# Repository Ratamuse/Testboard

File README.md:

## Testboard V2.2 ESP32

## Carte multi-usage basée sur le module ESP-WROOM-32E:

- Connecteur USB-C

- Chargeur solaire MPPT basé sur la puce CN3791:  http://www.consonance-elec.com/pdf/datasheet/DSE-CN3791.pdf

- Connecteur batterie JST-PH 2mm avec protection (surcharge ou décharge profonde)

- Connecteur batterie JST-PH 2mm sans protection (pour batterie déjà protégée)

- Bouton on/off LTC2954 avec interrupt sur µP (On/Off de l'ESP32 et GPIO de l'interrupt utilisable pour des actions): https://www.analog.com/media/en/technical-documentation/data-sheets/2954fb.pdf

- Capteur BOSCH BME680: https://www.bosch-sensortec.com/products/environmental-sensors/gas-sensors/bme680/

- 10 optocoupleurs pour interrupteurs à contacts secs (pour domotiser volets roulants, télécommandes diverses) ou au choix 10 GPIO dispo avec au choix alim 3.3V ou "5V" (Vbat (entre 3.2 et 4.2V) ou Vbus (5V)) pour ajouter des modules.

- Chargeur Li-io/Li-Po MCP73831 via port USB-C

- Connecteur JST-PH 2mm (1x4) I2C

- Connecteur JST-PH 2mm (1x4) sur 2 GPIO + choix 3.3V ou 5V

- Connecteur JST-PH 2mm (1x3) sur 1 GPIO (que j'utilise pour piloter des leds neopixel)

Inspiration des travaux de Lilygo, Waveshare, GreatScoot.

Motivation et champs des possibles donnés par P. Demerliac et sa chaine Youtube Cyrob: https://www.youtube.com/channel/UC5QPFDZ3Y4ylkkGJc6Y1OOA  

Initiation à la bricole par P. W. Trainer

Prochaine étape, améliorer le hardaware du GNUVario-E

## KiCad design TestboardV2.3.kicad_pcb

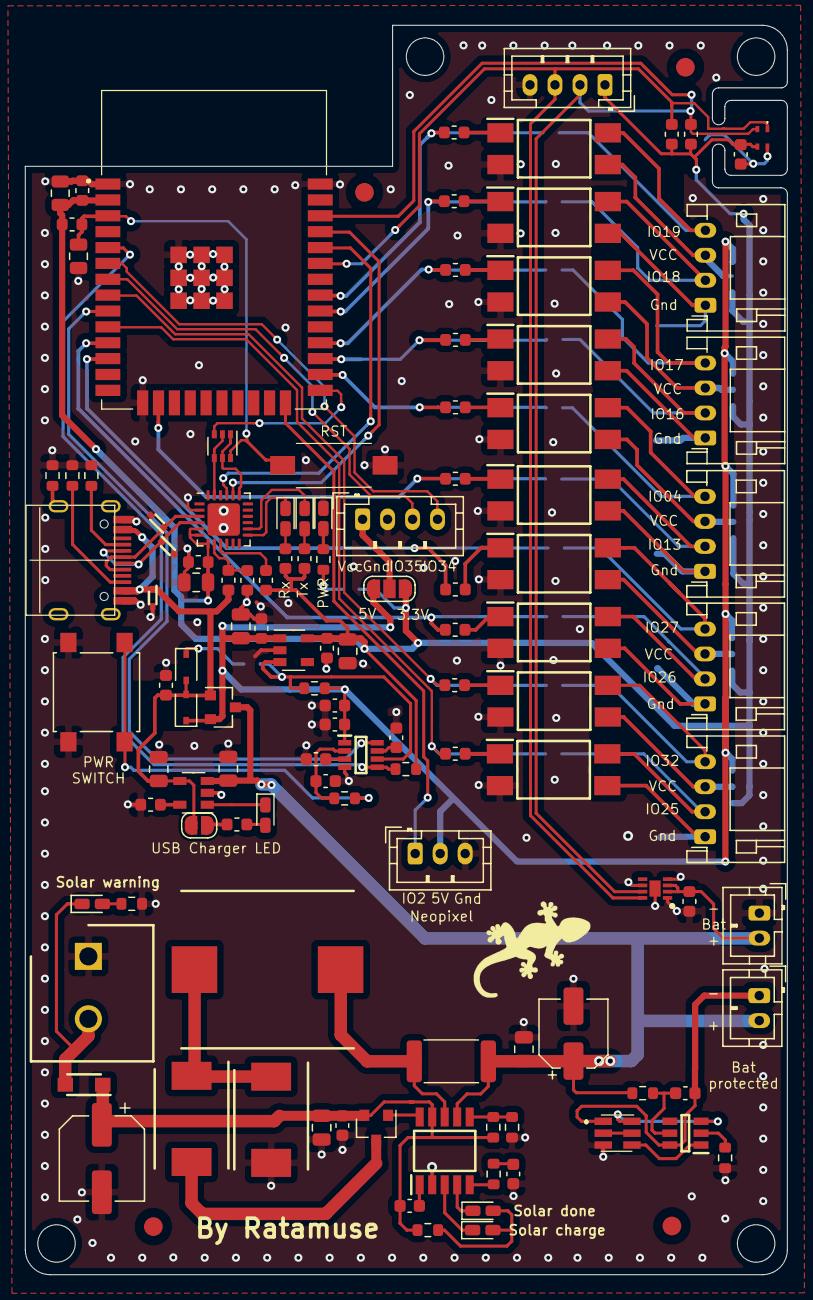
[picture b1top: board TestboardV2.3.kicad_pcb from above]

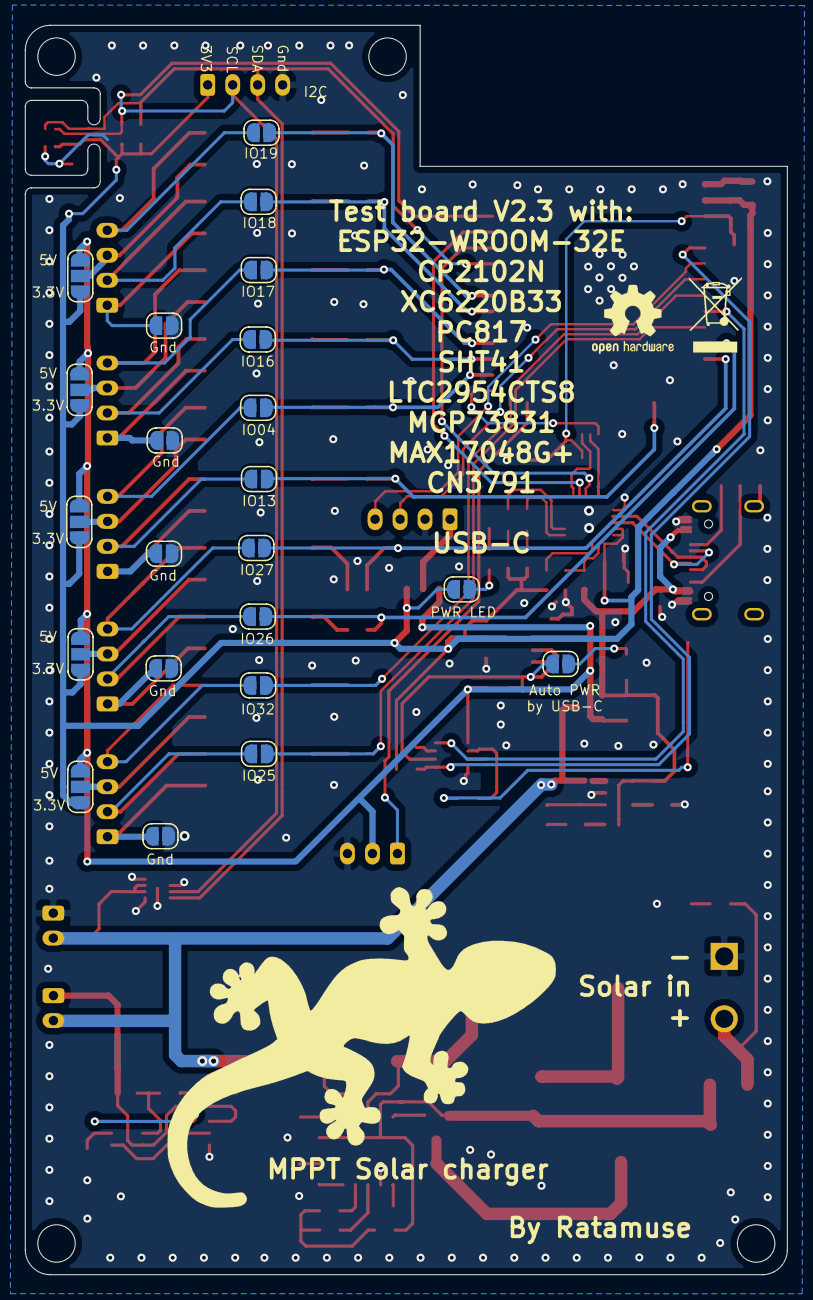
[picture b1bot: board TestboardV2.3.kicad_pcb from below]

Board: 2 copper layers, 61.0 x 100.0 mm, 143 parts (22 on the bottom side), 102 nets.

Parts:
C1, C3: 22µF; C_0805_2012Metric
C2, C5, C7, C9, C11, C15, C18, C20, C27: 0.1µF; C_0603_1608Metric
C4: 1µF; C_0603_1608Metric
C6, C16, C17: 4.7µF; C_0805_2012Metric
C8, C10: 0.150µF; C_0603_1608Metric
C12: 100µF/35V; CP_Elec_6.3x7.7
C13: 470nF/50V; C_0603_1608Metric
C14: 4.7µF/50V; C_0805_2012Metric
C19: 220nF; C_0603_1608Metric
C21: 0.1µF/50V; C_0603_1608Metric
C22, C24, C25: 10µF; C_0805_2012Metric
C23: 10µF; CP_Elec_5x5.4
D1, D2, D3: SP1003-01DTG; SODFL1406X65N
D4, D14: D_Schottky; D_SOD-323
D5, D6, D7, D8, D10, D11: LED; LED_0603_1608Metric_Castellated
D9: MBR230LSFT1G; SODFL3616X98N
D12, D13: SS34; DIOM8059X256N
D15: LED Green; LED_0603_1608Metric_Castellated
FID1, FID2, FID3, FID4: Fiducial; Fiducial_1.5mm_Mask3mm
IC1: CN3791; SOP100P600X175-10N
IC2: MAX17048G+; SON50P200X200X80-9N-D
IC3: LTC2954CTS8-1#TRMPBF; SOT65P280X100-8N
IC4: FS312F-G; SOT95P280X145-6N
IC6: SHT41-AD1B-R3; SHT41AD1BR3
J1: Conn_01x02; SHDR2W90P0X500_1X2_1060X980X1380P
J2, J3, J4, J5, J6: Conn_01x04_MountingPin; JST_PH_S4B-PH-K_1x04_P2.00mm_Horizontal_ratamuse
J7, J10: Conn_01x04; JST_PH_B4B-PH-K_1x04_P2.00mm_Vertical
J8, J12: Conn_01x02; JST_PH_B2B-PH-K_1x02_P2.00mm_Vertical
J9: Conn_01x03; JST_PH_B3B-PH-K_1x03_P2.00mm_Vertical
J13: USB_C_Receptacle_USB2.0 USB4105-GF-A; TYPE-C-31-M-12
JP1, JP2, JP3, JP4, JP5, JP6, JP7, JP8, JP9, JP10, JP11, JP12, JP15, JP16, JP17, JP21, JP24: SolderJumper_2_Open; SolderJumper-2_P1.3mm_Open_RoundedPad1.0x1.5mm
JP13, JP14, JP18, JP19, JP20, JP23: SolderJumper_3_Open; SolderJumper-3_P1.3mm_Open_RoundedPad1.0x1.5mm_NumberLabels
JP22: Jumper_2_Open; SolderJumper-2_P1.3mm_Open_RoundedPad1.0x1.5mm
L1: 82µH/3A; INDPM138126X700N
Q1: UMH3N; SOT-363_SC-70-6
Q2: DMG2301L; SOT-23
Q3: AO3401A; SOT-23
Q4: FS8205
R1, R15, R19, R25, R27, R29: 10K; R_0603_1608Metric
R2, R3, R4, R5, R6, R7, R8, R9, R10, R11, R14, R21, R22, R30: 1K; R_0603_1608Metric
R12: 22.1K; R_0603_1608Metric
R13: 47.5k; R_0603_1608Metric
R16, R17: 2.2K; R_0603_1608Metric
R18, R35: 2K; R_0603_1608Metric
R20: 330; R_0603_1608Metric
R23: 30K; R_0603_1608Metric
R24: 120; R_0603_1608Metric
R26: 1M; R_0603_1608Metric
R28: 0.24R; R_2512_6332Metric
R31: 100; R_0603_1608Metric
R33, R34, R36: 5.1K; R_0603_1608Metric
R37: 100K; R_0603_1608Metric
SW1: SW_Push; PTS636SL43SMTRLFS
SW2: SW_Push; SW_SPST_B3S-1000
U1: ESP32-WROOM-32D; ESP32WROOM32EM113EH2800PH3Q0
U2, U3, U4, U5, U6, U7, U8, U9, U10, U11: PC817; SOP254P960X420-4N
U12: CP2102N-A02-GQFN24; QFN-24-1EP_4x4mm_P0.5mm_EP2.6x2.6mm
U13: XC6220B331MR; SOT-23-5
U15: MCP73831-2-OT; SOT-23-5

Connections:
+3V3: C1.1, C2.1, C6.1, C7.1, C11.1, C20.1, C25.1, IC6.3, J7.1, JP13.3, JP14.3, JP18.3, JP19.3, JP20.3, JP21.1, JP23.1, R1.1, R14.2, R15.1, R16.2, R17.2, R21.2, R22.2, U1.2, U12.5, U12.6, U12.7, U13.5
+5V: C4.1, C5.1, C9.1, C24.1, D4.1, IC3.1, J9.2, JP13.1, JP14.1, JP18.1, JP19.1, JP20.1, JP23.3, Q2.2, R37.2, U13.1
CE: IC3.6, JP24.2, R37.1, U13.3
DTR: Q1.2, Q1.4, U12.23
GND: C1.2, C2.2, C3.2, C4.2, C5.2, C6.2, C7.2, C8.2, C9.2, C10.2, C11.2, C12.2, C13.2, C14.2, C15.2, C16.2, C17.2, C18.2, C19.2, C20.2, C22.2, C23.2, C24.2, C25.2, D1.2, D2.2, D3.2, D12.2, D15.1, IC1.2, IC2.1, IC2.4, IC2.6, IC2.9, IC3.4, IC6.4, J1.1, J7.4, J9.3, J10.2, J12.1, J13.A1, J13.A12, J13.B1, J13.B12, JP11.2, JP12.2, JP15.2, JP16.2, JP17.2, Q4.3, R13.1, R18.2, R19.2, R26.1, R27.2, R30.2, R33.1, R34.1, R35.2, SW1.2, SW2.1, U1.1, U1.15, U1.38, U1.39, U2.2, U3.2, U4.2, U5.2, U6.2, U7.2, U8.2, U9.2, U10.2, U11.2, U12.2, U12.25, U13.2, U15.2
IO0: Q1.3, U1.25
IO2: J9.1, U1.24
IO04: JP5.1, R6.2, U1.26
IO13: JP6.1, R7.2, U1.16
IO16: JP4.1, R5.2, U1.27
IO17: JP3.1, R4.2, U1.28
IO18: JP2.1, R3.2, U1.30
IO19: JP1.1, R2.2, U1.31
IO25: JP10.1, R11.2, U1.10
IO26: JP8.1, R9.2, U1.11
IO27: JP7.1, R8.2, U1.12
IO32: JP9.1, R10.2, U1.8
IO34: J10.4, U1.6
IO35: J10.3, U1.7
unnamed: C8.1, IC3.3
unnamed: C10.1, IC3.7
unnamed: C15.1, IC3.2, R36.1
unnamed: C19.1, R24.2
unnamed: C21.2, IC1.1
unnamed: C27.1, IC4.5, R31.2
unnamed: D5.1, U15.1
unnamed: D5.2, R20.2
unnamed: D6.2, R21.1
unnamed: D7.2, R22.1
unnamed: D8.1, D9.2, J1.2
unnamed: D8.2, R35.1
unnamed: D10.1, IC1.3
unnamed: D10.2, D11.2, R25.2
unnamed: D11.1, IC1.4
unnamed: D12.1, D13.1, L1.1
unnamed: D13.2, Q3.3
unnamed: D14.1, JP24.1
unnamed: D15.2, R29.1
unnamed: IC1.5, R24.1
unnamed: IC1.6, R23.2, R27.1
unnamed: IC1.8, L1.2, R28.1
unnamed: IC1.10, Q3.1
unnamed: IC4.1, Q4.6
unnamed: IC4.2, R30.1
unnamed: IC4.3, Q4.4
unnamed: J2.1, JP1.2, U2.4
unnamed: J2.2, JP13.2, U2.3
unnamed: J2.3, JP2.2, U3.4
unnamed: J2.4, JP11.1, U3.3
unnamed: J3.1, JP3.2, U4.4
unnamed: J3.2, JP14.2, U4.3
unnamed: J3.3, JP4.2, U5.4
unnamed: J3.4, JP12.1, U5.3
unnamed: J4.1, JP5.2, U6.4
unnamed: J4.2, JP18.2, U6.3
unnamed: J4.3, JP6.2, U7.4
unnamed: J4.4, JP15.1, U7.3
unnamed: J5.1, JP7.2, U8.4
unnamed: J5.2, JP19.2, U8.3
unnamed: J5.3, JP8.2, U9.4
unnamed: J5.4, JP16.1, U9.3
unnamed: J6.1, JP9.2, U10.4
unnamed: J6.2, JP20.2, U10.3
unnamed: J6.3, JP10.2, U11.4
unnamed: J6.4, JP17.1, U11.3
unnamed: J10.1, JP23.2
unnamed: J13.A5, R33.2
unnamed: J13.B5, R34.2
unnamed: J13.S1, R26.2
unnamed: JP21.2, R29.2
unnamed: JP22.2, R20.1
unnamed: Q4.2, Q4.5
unnamed: R2.1, U2.1
unnamed: R3.1, U3.1
unnamed: R4.1, U4.1
unnamed: R5.1, U5.1
unnamed: R6.1, U6.1
unnamed: R7.1, U7.1
unnamed: R8.1, U8.1
unnamed: R9.1, U9.1
unnamed: R10.1, U10.1
unnamed: R11.1, U11.1
unnamed: R12.1, R13.2, U12.8
unnamed: R14.1, U12.9
unnamed: R18.1, U15.5
unnamed: R36.2, SW2.2
PS_HOLD_IO33: IC3.8, U1.9
RST_EN: C3.1, Q1.6, R1.2, SW1.1, U1.3
RTS: Q1.1, Q1.5, U12.19
RXLED: D6.1, U12.13
SCL: IC2.7, IC6.2, J7.2, R17.1, U1.36
SDA: IC2.8, IC6.1, J7.3, R16.1, U1.33
Sensor_VN_IO39: IC3.5, R15.2, U1.5
TXLED: D7.1, U12.14
UORXD: U1.34, U12.21
UOTXD: U1.35, U12.20
USBD_N: D3.1, J13.A7, J13.B7, U12.4
USBD_P: D2.1, J13.A6, J13.B6, U12.3
VBAT: C17.1, C18.1, C22.1, C23.1, IC1.7, IC2.2, IC2.3, J8.2, J12.2, Q2.3, R28.2, R31.1, U15.3
VBAT-: C27.2, IC4.6, J8.1, Q4.1
VBUS: C16.1, D1.1, D4.2, D14.2, J13.A4, J13.A9, J13.B4, J13.B9, JP22.1, Q2.1, R12.2, R19.1, U15.4
Vsolar: C12.1, C13.1, C14.1, C21.1, D9.1, IC1.9, Q3.2, R23.1, R25.1

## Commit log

2021-10-16 Folder update
2021-10-16 Pictures
2021-10-16 Ajout BOM
2021-10-18 BOM updated Add comments on PCB drawing (solar charger)
2021-10-28 Added LDO CE Pullup. JLCPCB files updated
2021-12-12 Testboard V2.3
2021-12-13 Gnd pad correction
2021-12-13 serigraphy correction
